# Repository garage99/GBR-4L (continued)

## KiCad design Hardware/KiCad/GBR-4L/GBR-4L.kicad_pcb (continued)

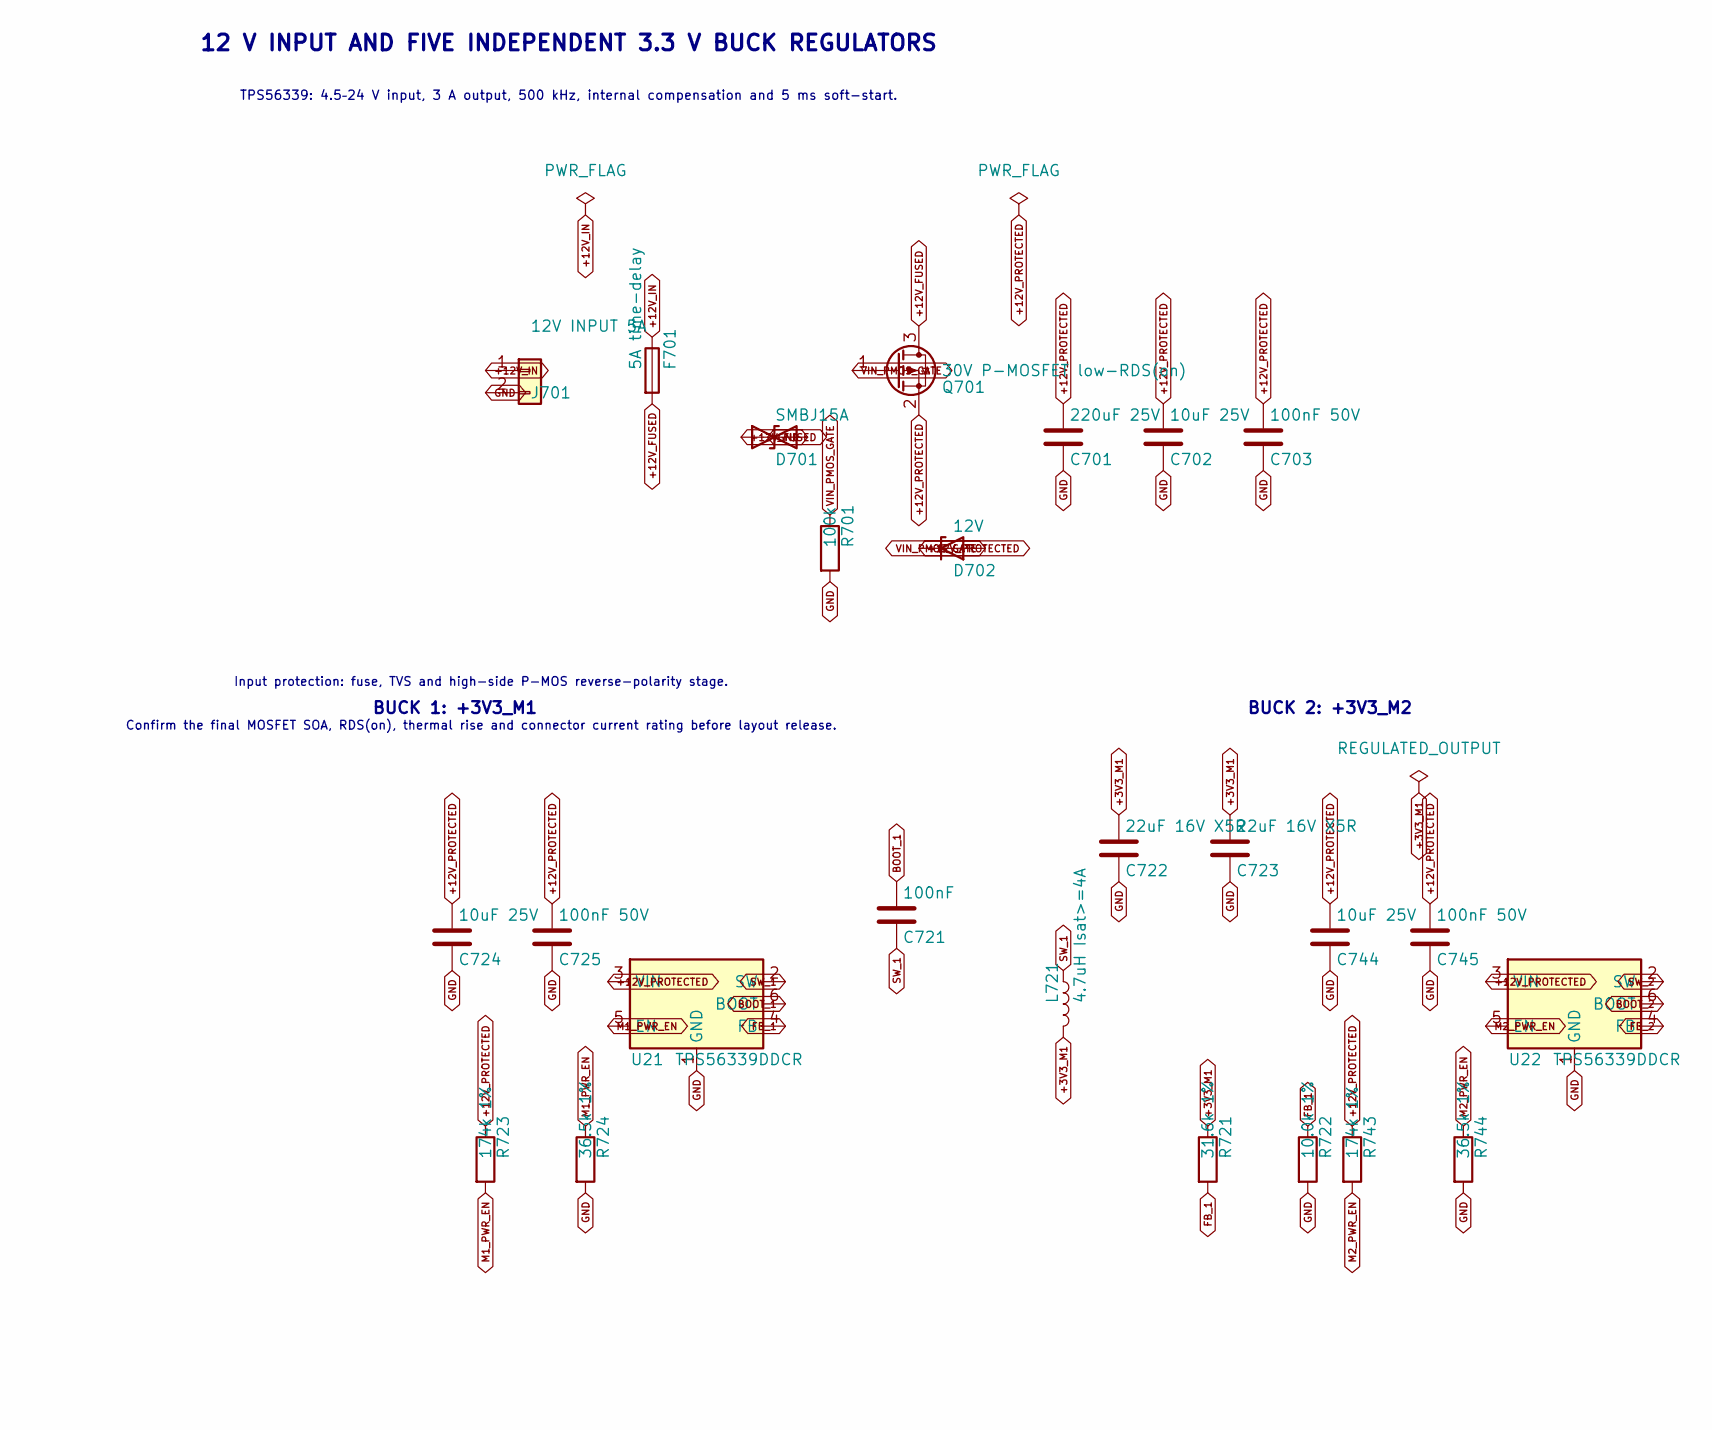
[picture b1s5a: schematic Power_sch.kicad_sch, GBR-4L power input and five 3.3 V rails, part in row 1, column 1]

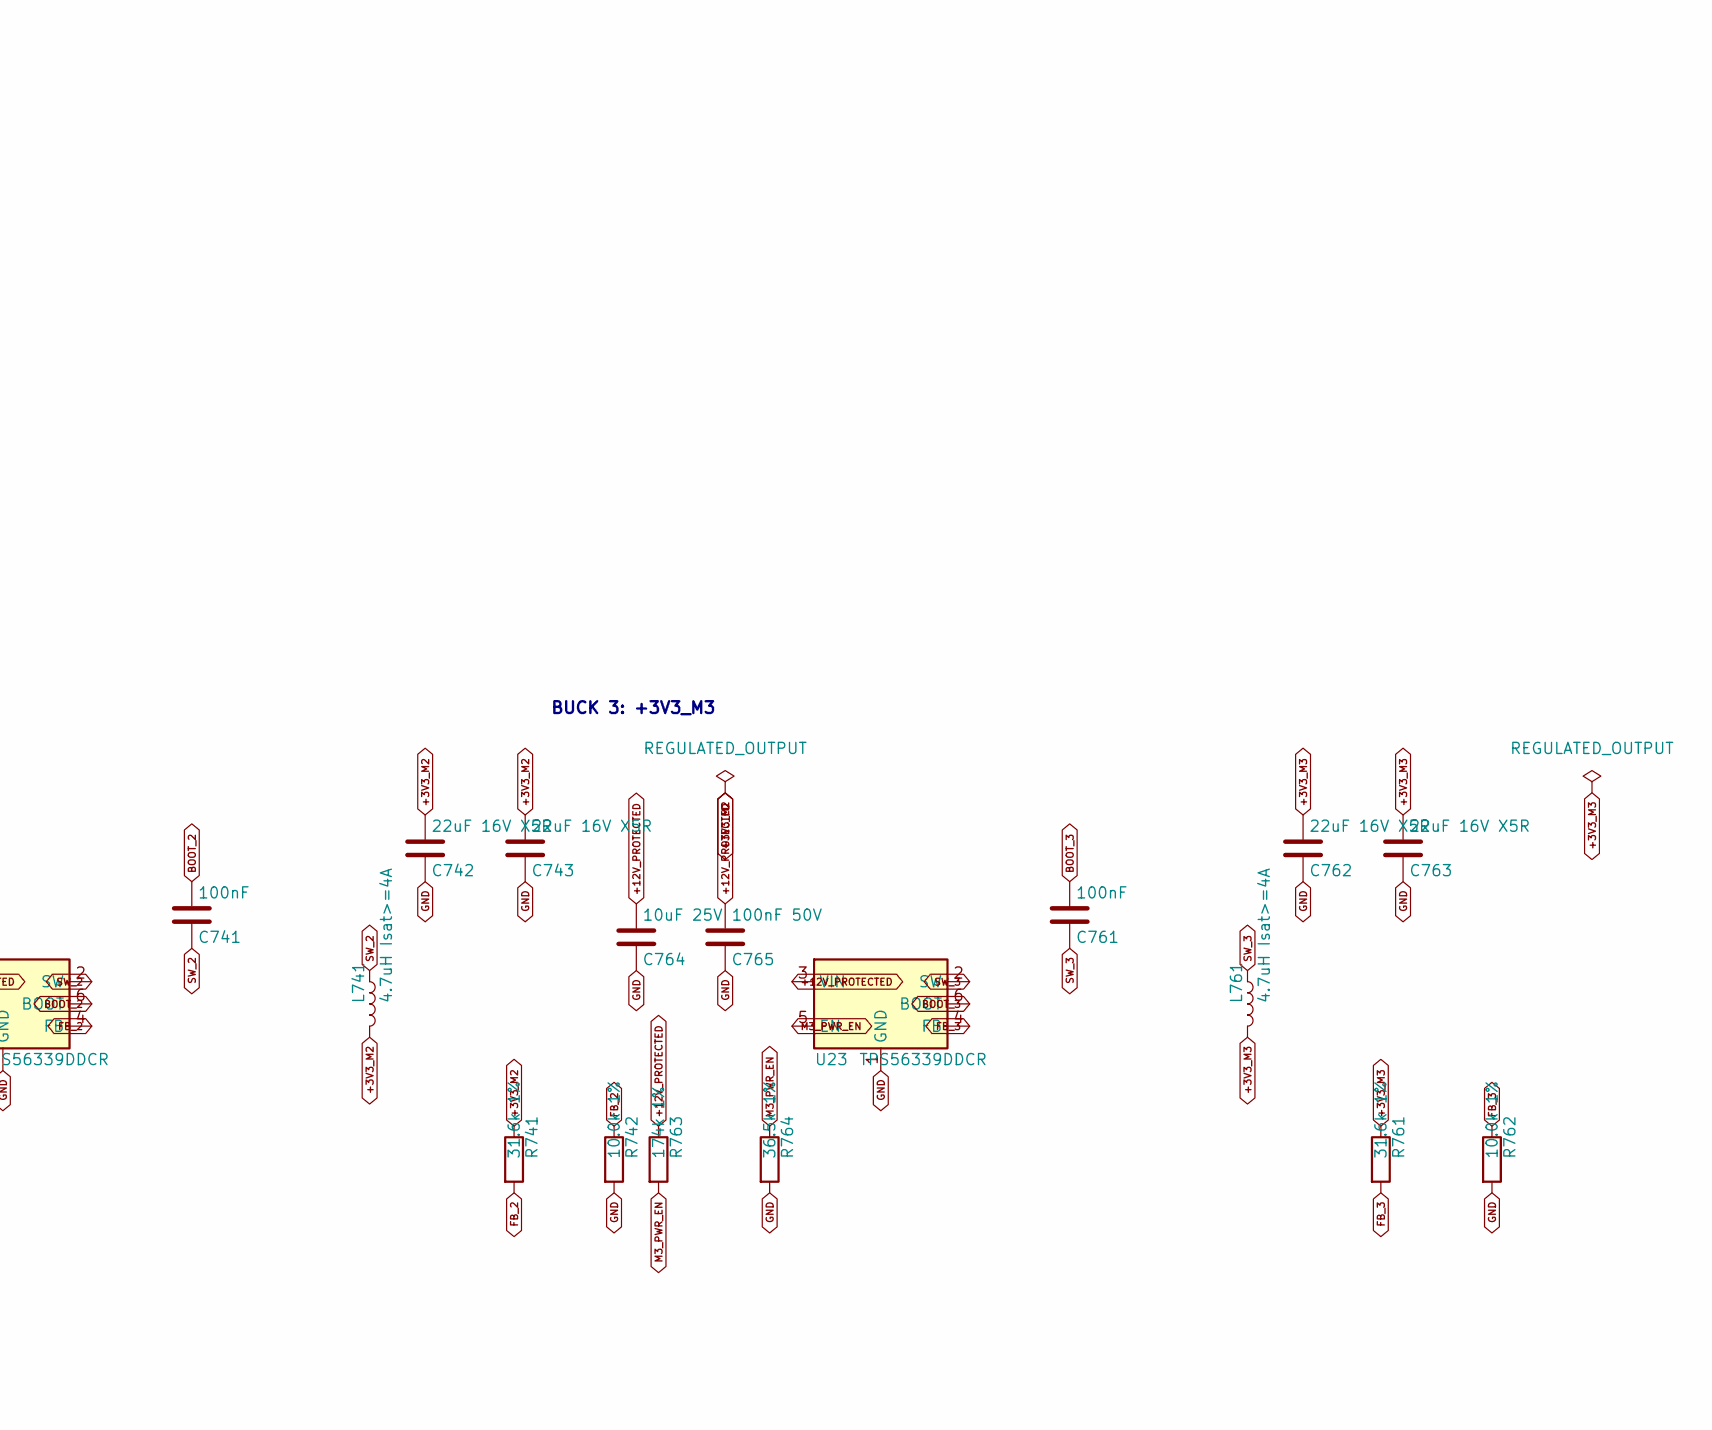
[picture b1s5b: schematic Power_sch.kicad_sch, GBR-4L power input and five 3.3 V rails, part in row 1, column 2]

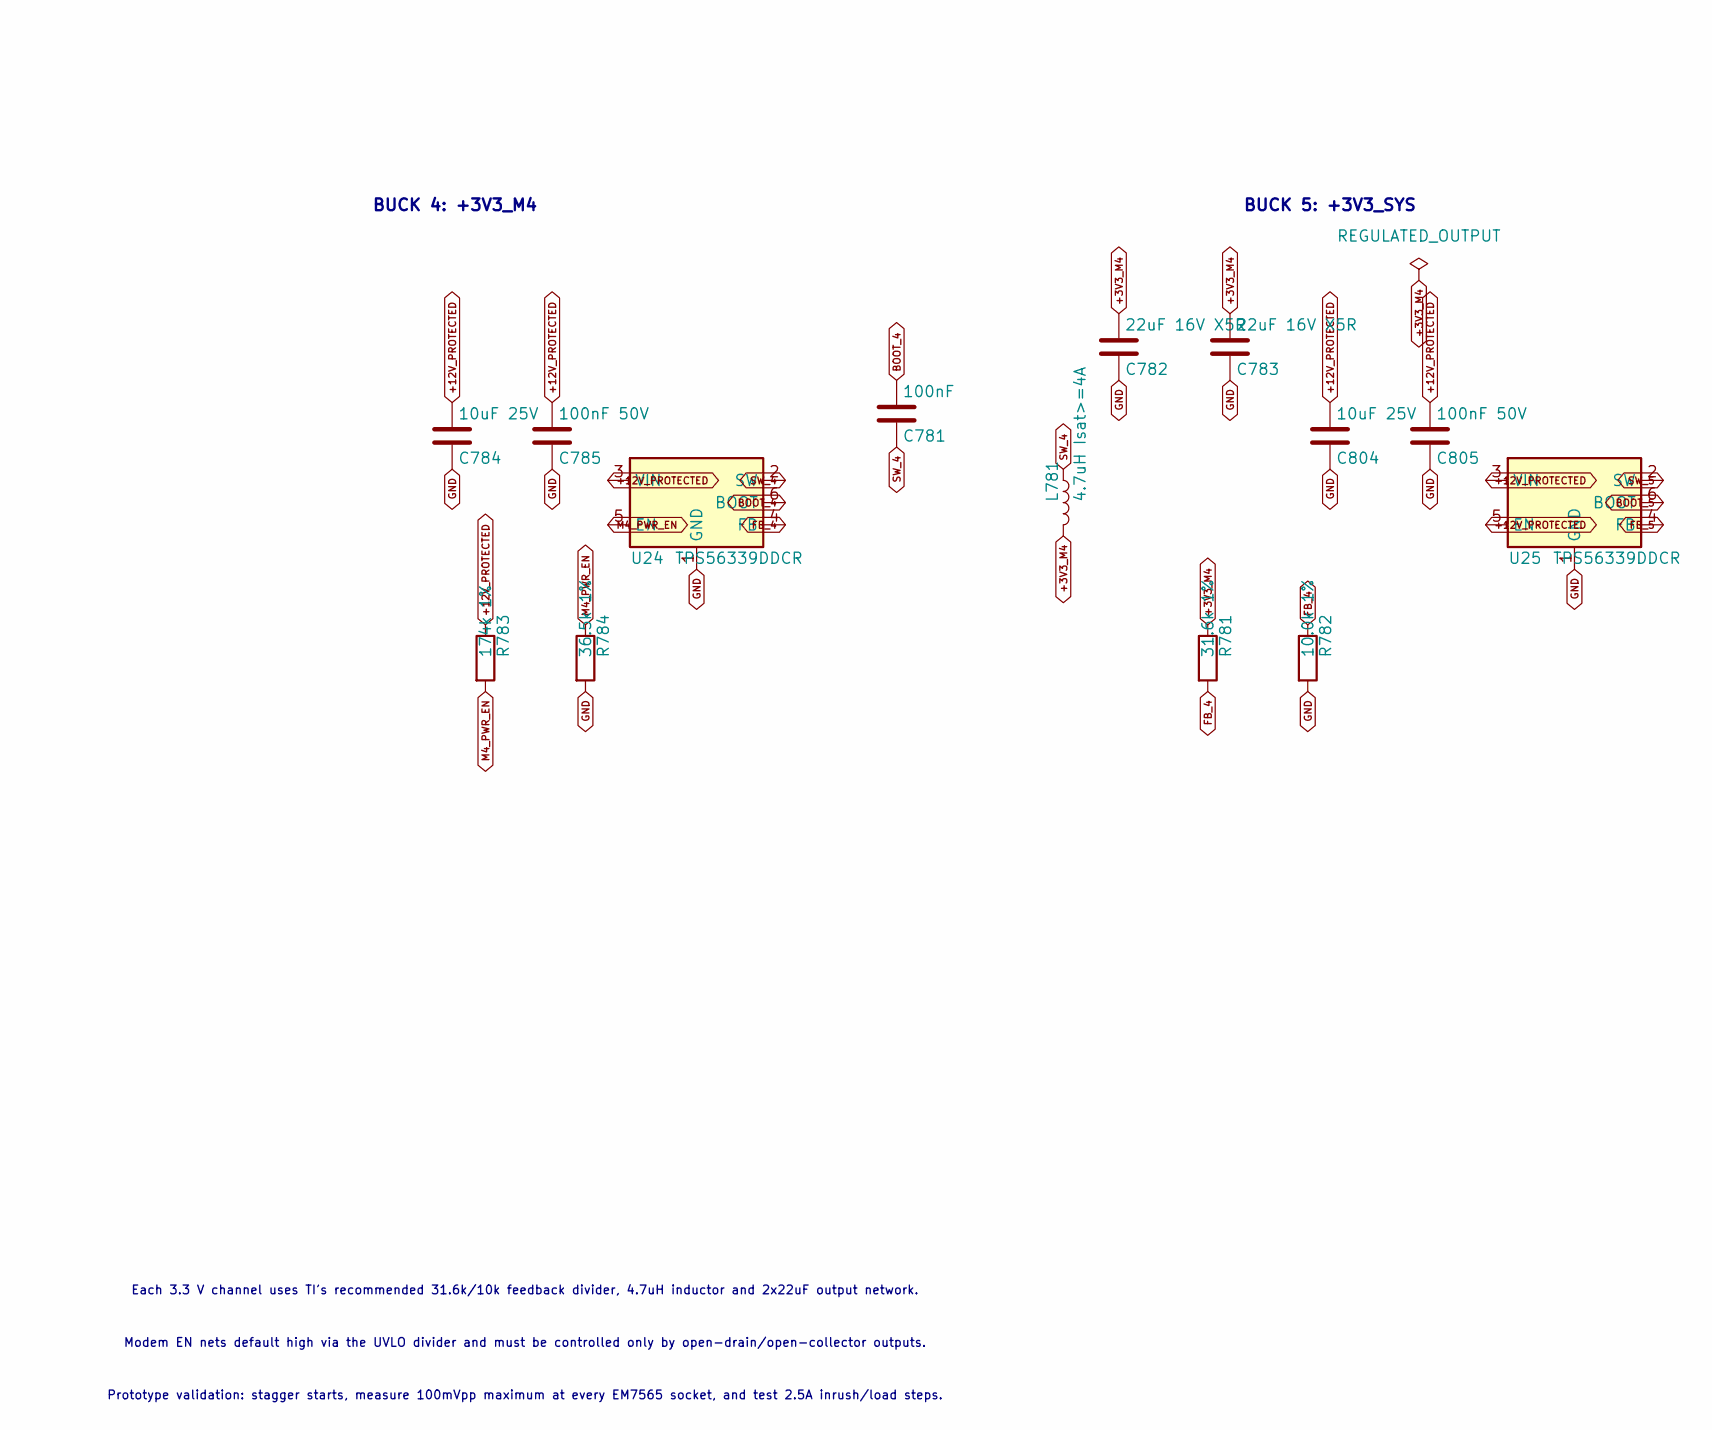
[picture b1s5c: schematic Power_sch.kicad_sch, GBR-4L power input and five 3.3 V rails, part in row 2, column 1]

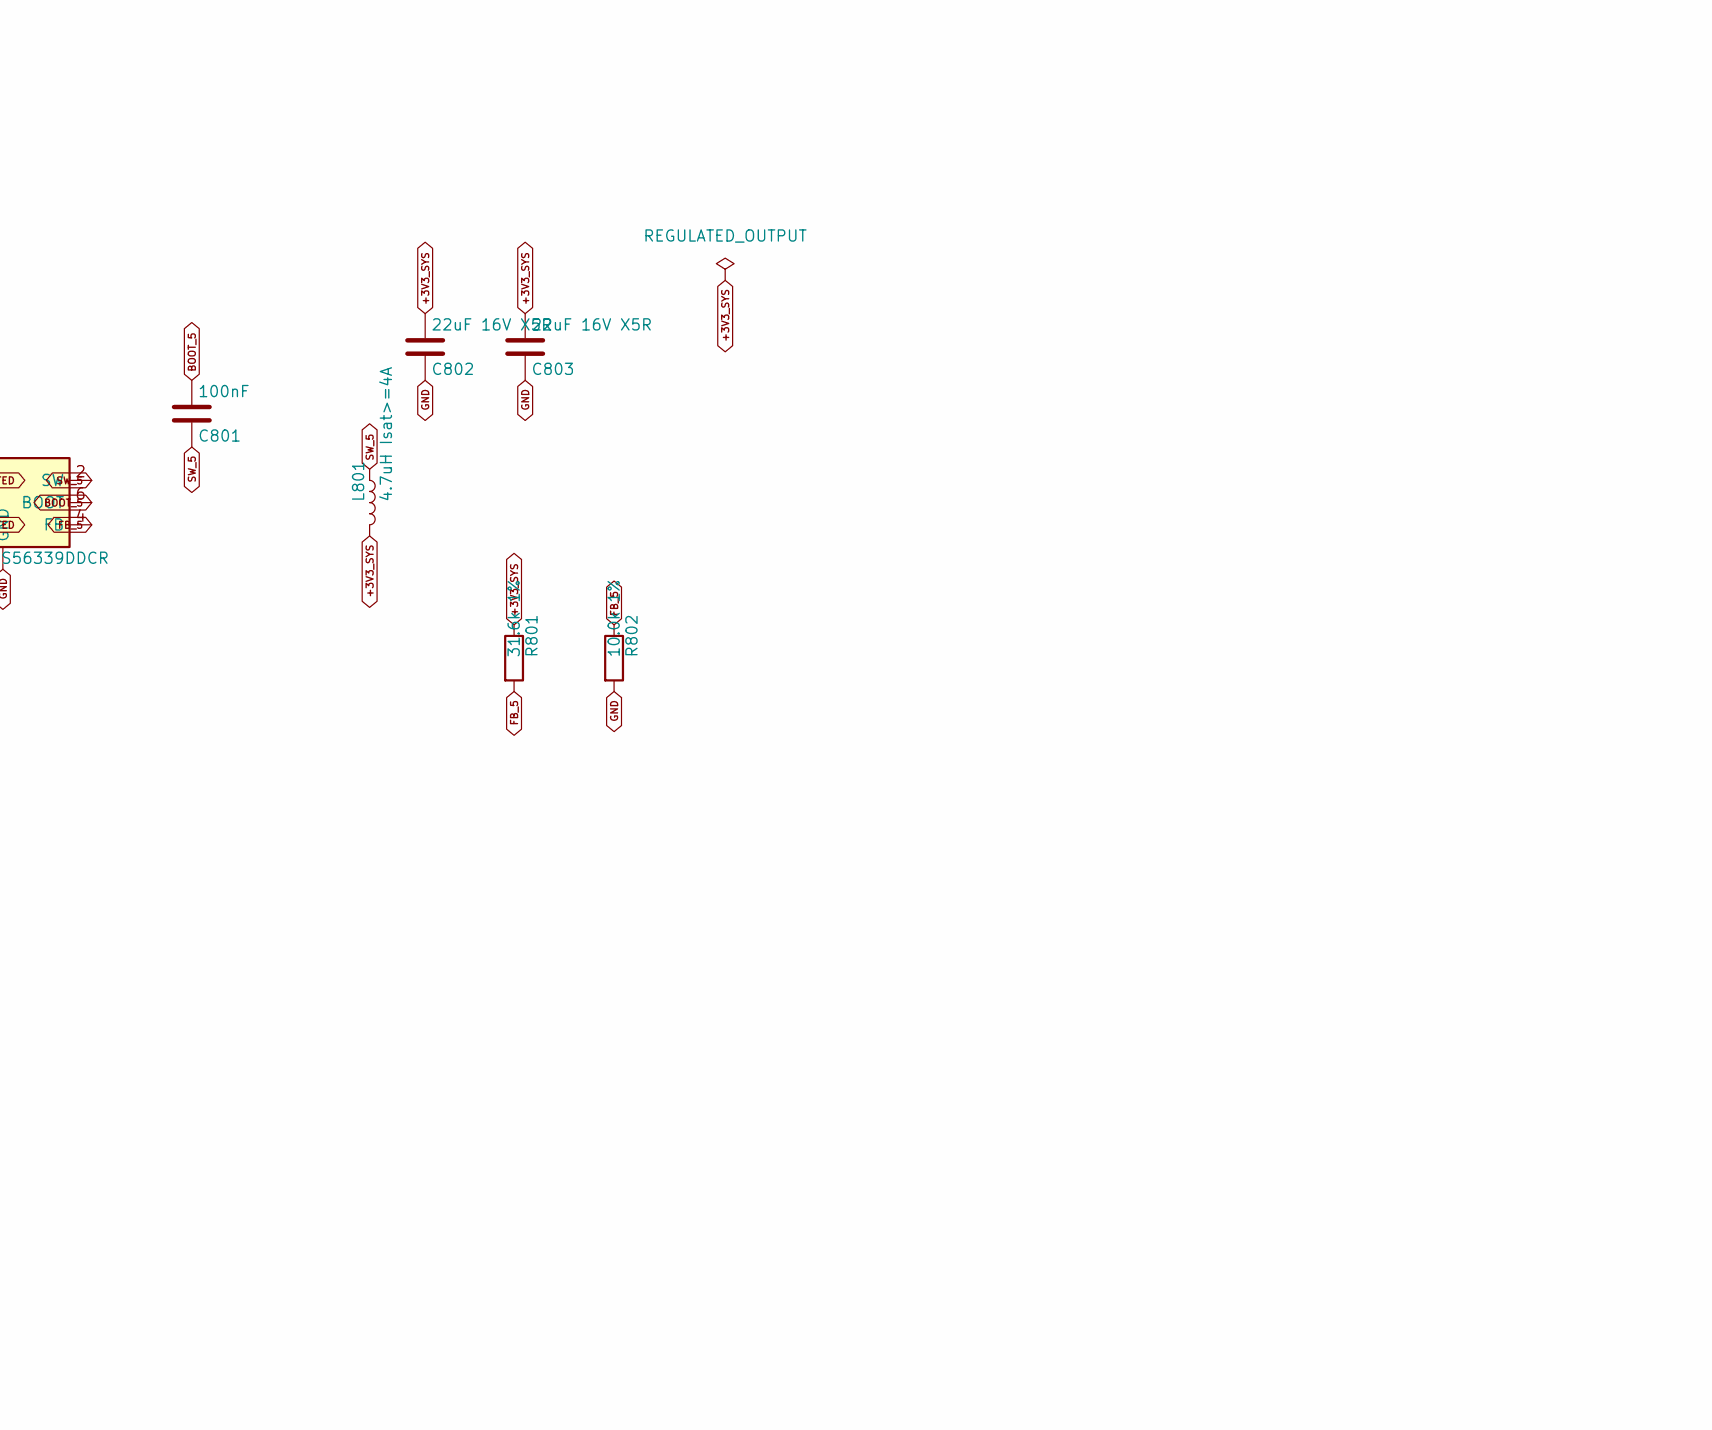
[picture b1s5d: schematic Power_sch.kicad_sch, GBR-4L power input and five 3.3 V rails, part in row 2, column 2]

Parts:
C701: 220uF 25V; C_Elec_10x10.2
C702: 10uF 25V; C_1210_3225Metric
C703, C725, C745, C765, C785, C805: 100nF 50V; C_0603_1608Metric
C721, C741, C761, C781, C801: 100nF; C_0603_1608Metric
C722, C723, C742, C743, C762, C763, C782, C783, C802, C803: 22uF 16V X5R; C_0805_2012Metric
C724, C744, C764, C784, C804: 10uF 25V; C_0805_2012Metric
D701: SMBJ15A; D_SMB
D702: 12V; D_SOD-123
F701: 5A time-delay; Fuseholder_Blade_ATO_Littelfuse_Pudenz_2_Pin
J701: 12V INPUT 5A; TerminalBlock_Phoenix_MKDS-1,5-2_1x02_P5.00mm_Horizontal
L721, L741, L761, L781, L801: 4.7uH Isat>=4A; L_7.3x7.3_H3.5
Q701: 30V P-MOSFET low-RDS(on); TO-252-2
R701: 100k; R_0603_1608Metric
R721, R741, R761, R781, R801: 31.6k 1%; R_0603_1608Metric
R722, R742, R762, R782, R802: 10.0k 1%; R_0603_1608Metric
R723, R743, R763, R783: 174k 1%; R_0603_1608Metric
R724, R744, R764, R784: 36.5k 1%; R_0603_1608Metric
U21, U22, U23, U24, U25: TPS56339DDCR; SOT-23-6

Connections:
+3V3_M1: C722.1, C723.1, L721.2, R721.1; also elsewhere on the board
+3V3_M2: C742.1, C743.1, L741.2, R741.1; also elsewhere on the board
+3V3_M3: C762.1, C763.1, L761.2, R761.1; also elsewhere on the board
+3V3_M4: C782.1, C783.1, L781.2, R781.1; also elsewhere on the board
+3V3_SYS: C802.1, C803.1, L801.2, R801.1; also elsewhere on the board
+12V_FUSED: D701.1 (A1), F701.2, Q701.3 (D)
+12V_IN: F701.1, J701.1
+12V_PROTECTED: C701.1, C702.1, C703.1, C724.1, C725.1, C744.1, C745.1, C764.1, C765.1, C784.1, C785.1, C804.1, C805.1, D702.1 (K), Q701.2 (S), R723.1, R743.1, R763.1, R783.1, U21.3 (VIN), U22.3 (VIN), U23.3 (VIN), U24.3 (VIN), U25.3 (VIN), U25.5 (EN)
BOOT_1: C721.1, U21.6 (BOOT)
BOOT_2: C741.1, U22.6 (BOOT)
BOOT_3: C761.1, U23.6 (BOOT)
BOOT_4: C781.1, U24.6 (BOOT)
BOOT_5: C801.1, U25.6 (BOOT)
FB_1: R721.2, R722.1, U21.4 (FB)
FB_2: R741.2, R742.1, U22.4 (FB)
FB_3: R761.2, R762.1, U23.4 (FB)
FB_4: R781.2, R782.1, U24.4 (FB)
FB_5: R801.2, R802.1, U25.4 (FB)
GND: C701.2, C702.2, C703.2, C722.2, C723.2, C724.2, C725.2, C742.2, C743.2, C744.2, C745.2, C762.2, C763.2, C764.2, C765.2, C782.2, C783.2, C784.2, C785.2, C802.2, C803.2, C804.2, C805.2, D701.2 (A2), J701.2, R701.2, R722.2, R724.2, R742.2, R744.2, R762.2, R764.2, R782.2, R784.2, R802.2, U21.1 (GND), U22.1 (GND), U23.1 (GND), U24.1 (GND), U25.1 (GND); also elsewhere on the board
M1_PWR_EN: R723.2, R724.1, U21.5 (EN); also elsewhere on the board
M2_PWR_EN: R743.2, R744.1, U22.5 (EN); also elsewhere on the board
M3_PWR_EN: R763.2, R764.1, U23.5 (EN); also elsewhere on the board
M4_PWR_EN: R783.2, R784.1, U24.5 (EN); also elsewhere on the board
SW_1: C721.2, L721.1, U21.2 (SW)
SW_2: C741.2, L741.1, U22.2 (SW)
SW_3: C761.2, L761.1, U23.2 (SW)
SW_4: C781.2, L781.1, U24.2 (SW)
SW_5: C801.2, L801.1, U25.2 (SW)
VIN_PMOS_GATE: D702.2 (A), Q701.1 (G), R701.1

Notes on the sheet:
Input protection: fuse, TVS and high-side P-MOS reverse-polarity stage.
Prototype validation: stagger starts, measure 100mVpp maximum at every EM7565 socket, and test 2.5A inrush/load steps.
BUCK 1: +3V3_M1
BUCK 4: +3V3_M4
Modem EN nets default high via the UVLO divider and must be controlled only by open-drain/open-collector outputs.
12 V INPUT AND FIVE INDEPENDENT 3.3 V BUCK REGULATORS
TPS56339: 4.5–24 V input, 3 A output, 500 kHz, internal compensation and 5 ms soft-start.
BUCK 5: +3V3_SYS
BUCK 3: +3V3_M3
Confirm the final MOSFET SOA, RDS(on), thermal rise and connector current rating before layout release.
BUCK 2: +3V3_M2
Each 3.3 V channel uses TI's recommended 31.6k/10k feedback divider, 4.7uH inductor and 2x22uF output network.

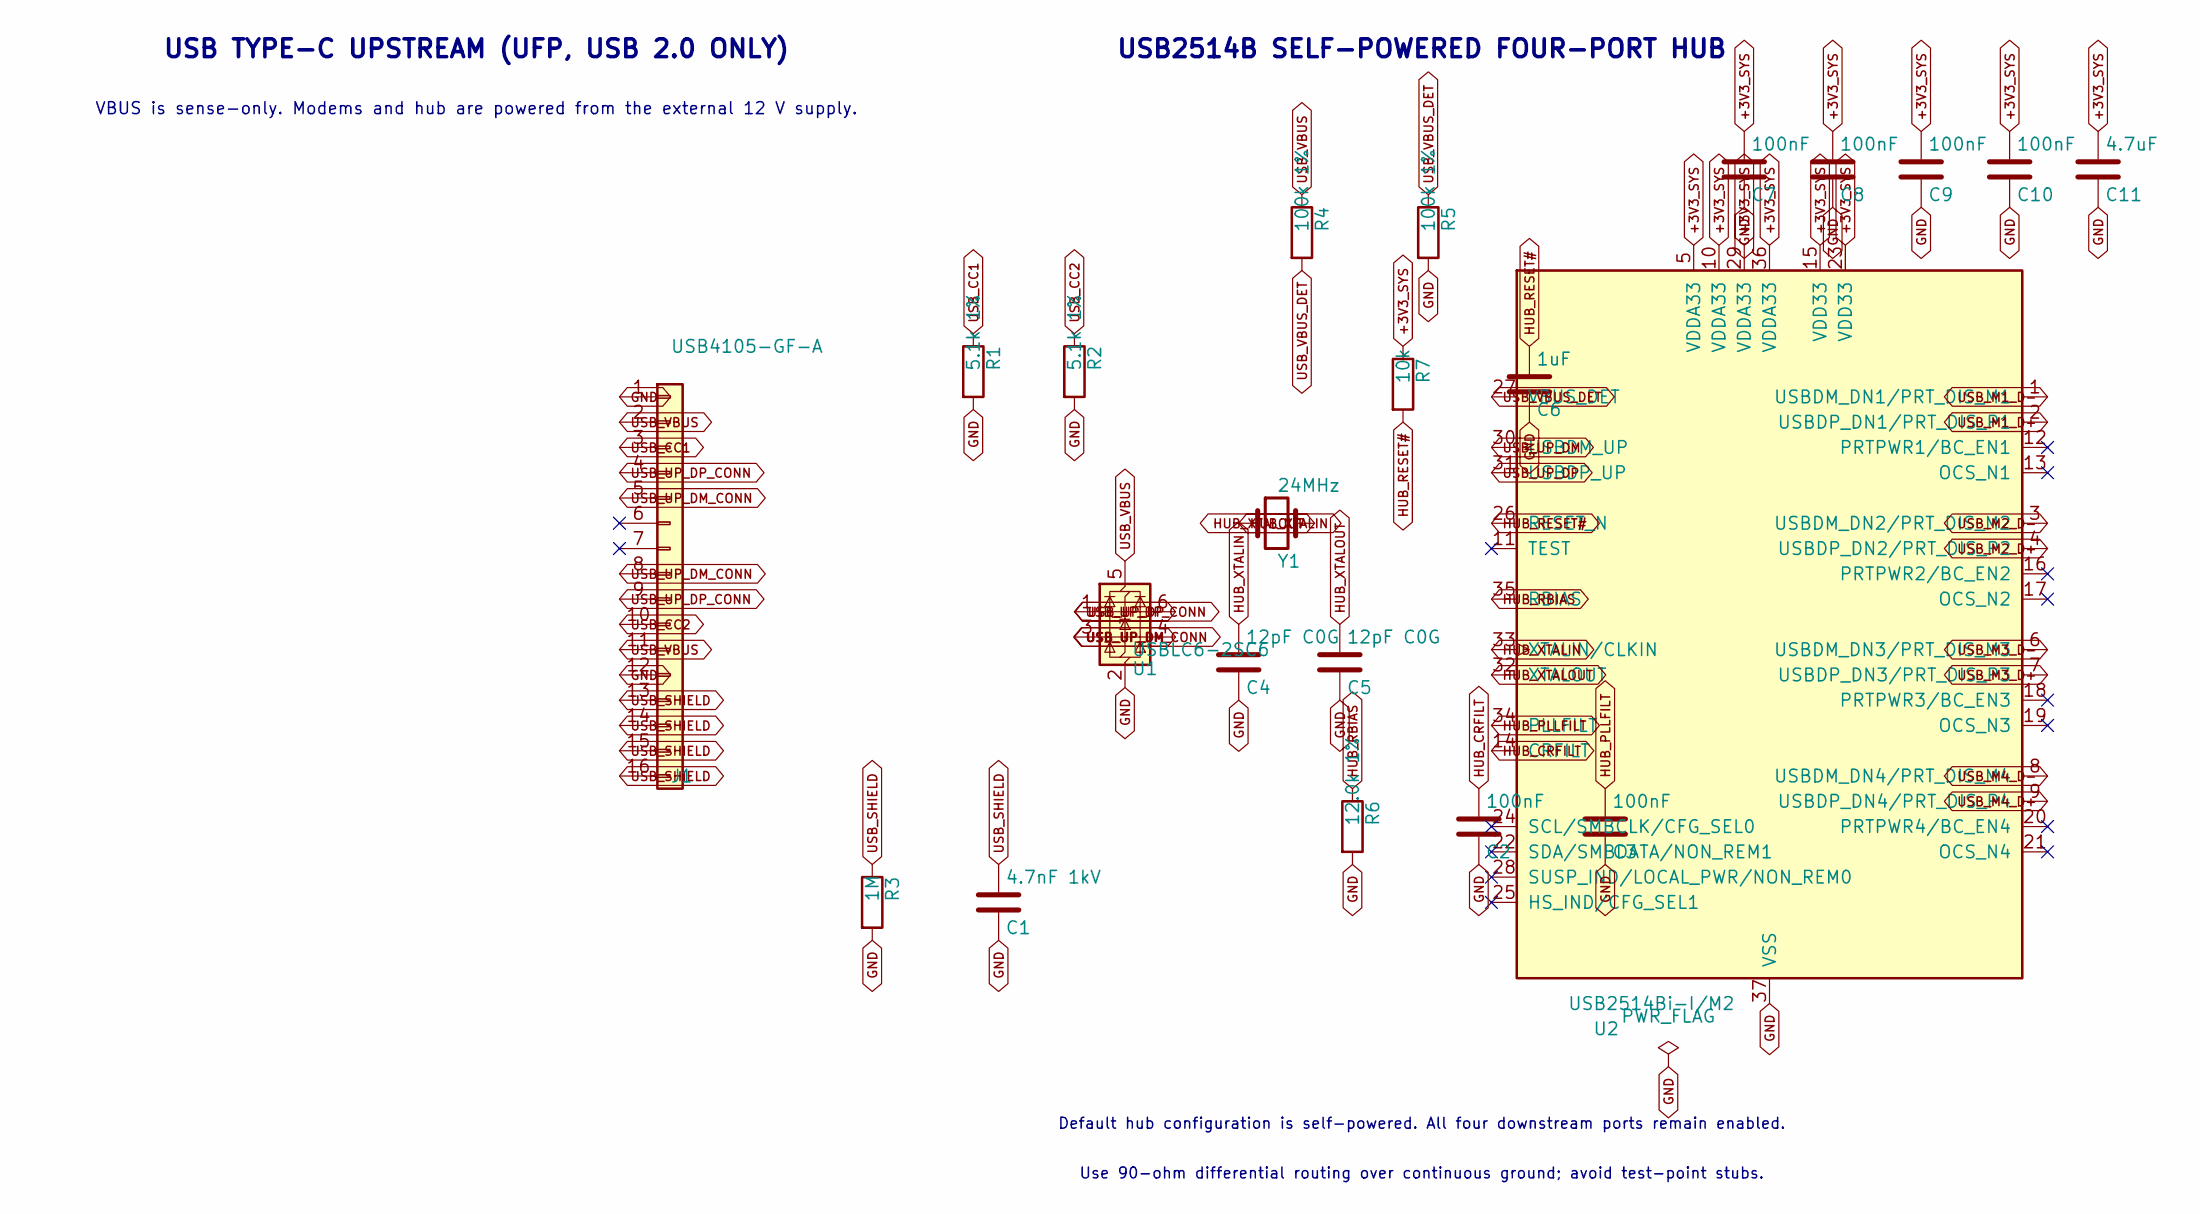
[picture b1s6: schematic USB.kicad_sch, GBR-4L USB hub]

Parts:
C1: 4.7nF 1kV; C_1206_3216Metric
C2, C3, C7, C8, C9, C10: 100nF; C_0603_1608Metric
C4, C5: 12pF C0G; C_0603_1608Metric
C6: 1uF; C_0603_1608Metric
C11: 4.7uF; C_0805_2012Metric
J1: USB4105-GF-A; GCT_USB4105-16P_MergedTails
R1, R2: 5.1k 1%; R_0603_1608Metric
R3: 1M; R_0603_1608Metric
R4, R5: 100k 1%; R_0603_1608Metric
R6: 12.0k 1%; R_0603_1608Metric
R7: 10k; R_0603_1608Metric
U1: USBLC6-2SC6; SOT-23-6
U2: USB2514Bi-I/M2; QFN-36-1EP_6x6mm_P0.5mm_EP4.1x4.1mm
Y1: 24MHz; Crystal_SMD_3225-4Pin_3.2x2.5mm

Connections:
+3V3_SYS: C7.1, C8.1, C9.1, C10.1, C11.1, R7.1, U2.5 (VDDA33), U2.10 (VDDA33), U2.15 (VDD33), U2.23 (VDD33), U2.29 (VDDA33), U2.36 (VDDA33); also elsewhere on the board
GND: C1.2, C2.2, C3.2, C4.2, C5.2, C6.2, C7.2, C8.2, C9.2, C10.2, C11.2, J1.1, J1.12, R1.2, R2.2, R3.2, R5.2, R6.2, U1.2 (GND), U2.37 (VSS); also elsewhere on the board
HUB_CRFILT: C2.1, U2.14 (CRFILT)
HUB_PLLFILT: C3.1, U2.34 (PLLFILT)
HUB_RBIAS: R6.1, U2.35 (RBIAS)
HUB_RESET#: C6.1, R7.2, U2.26 (RESET_N)
HUB_XTALIN: C4.1, U2.33 (XTALIN/CLKIN), Y1.1
HUB_XTALOUT: C5.1, U2.32 (XTALOUT), Y1.2
USB_CC1: J1.3, R1.1
USB_CC2: J1.10, R2.1
USB_M1_D+: U2.2 (USBDP_DN1/PRT_DIS_P1); also elsewhere on the board
USB_M1_D-: U2.1 (USBDM_DN1/PRT_DIS_M1); also elsewhere on the board
USB_M2_D+: U2.4 (USBDP_DN2/PRT_DIS_P2); also elsewhere on the board
USB_M2_D-: U2.3 (USBDM_DN2/PRT_DIS_M2); also elsewhere on the board
USB_M3_D+: U2.7 (USBDP_DN3/PRT_DIS_P3); also elsewhere on the board
USB_M3_D-: U2.6 (USBDM_DN3/PRT_DIS_M3); also elsewhere on the board
USB_M4_D+: U2.9 (USBDP_DN4/PRT_DIS_P4); also elsewhere on the board
USB_M4_D-: U2.8 (USBDM_DN4/PRT_DIS_M4); also elsewhere on the board
USB_SHIELD: C1.1, J1.13, J1.14, J1.15, J1.16, R3.1
USB_UP_DM: U1.4 (I/O2), U2.30 (USBDM_UP)
USB_UP_DM_CONN: J1.5, J1.8, U1.3 (I/O2)
USB_UP_DP: U1.6 (I/O1), U2.31 (USBDP_UP)
USB_UP_DP_CONN: J1.4, J1.9, U1.1 (I/O1)
USB_VBUS: J1.2, J1.11, R4.1, U1.5 (VBUS)
USB_VBUS_DET: R4.2, R5.1, U2.27 (VBUS_DET)

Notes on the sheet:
USB TYPE-C UPSTREAM (UFP, USB 2.0 ONLY)
USB2514B SELF-POWERED FOUR-PORT HUB
VBUS is sense-only. Modems and hub are powered from the external 12 V supply.
Default hub configuration is self-powered. All four downstream ports remain enabled.
Use 90-ohm differential routing over continuous ground; avoid test-point stubs.

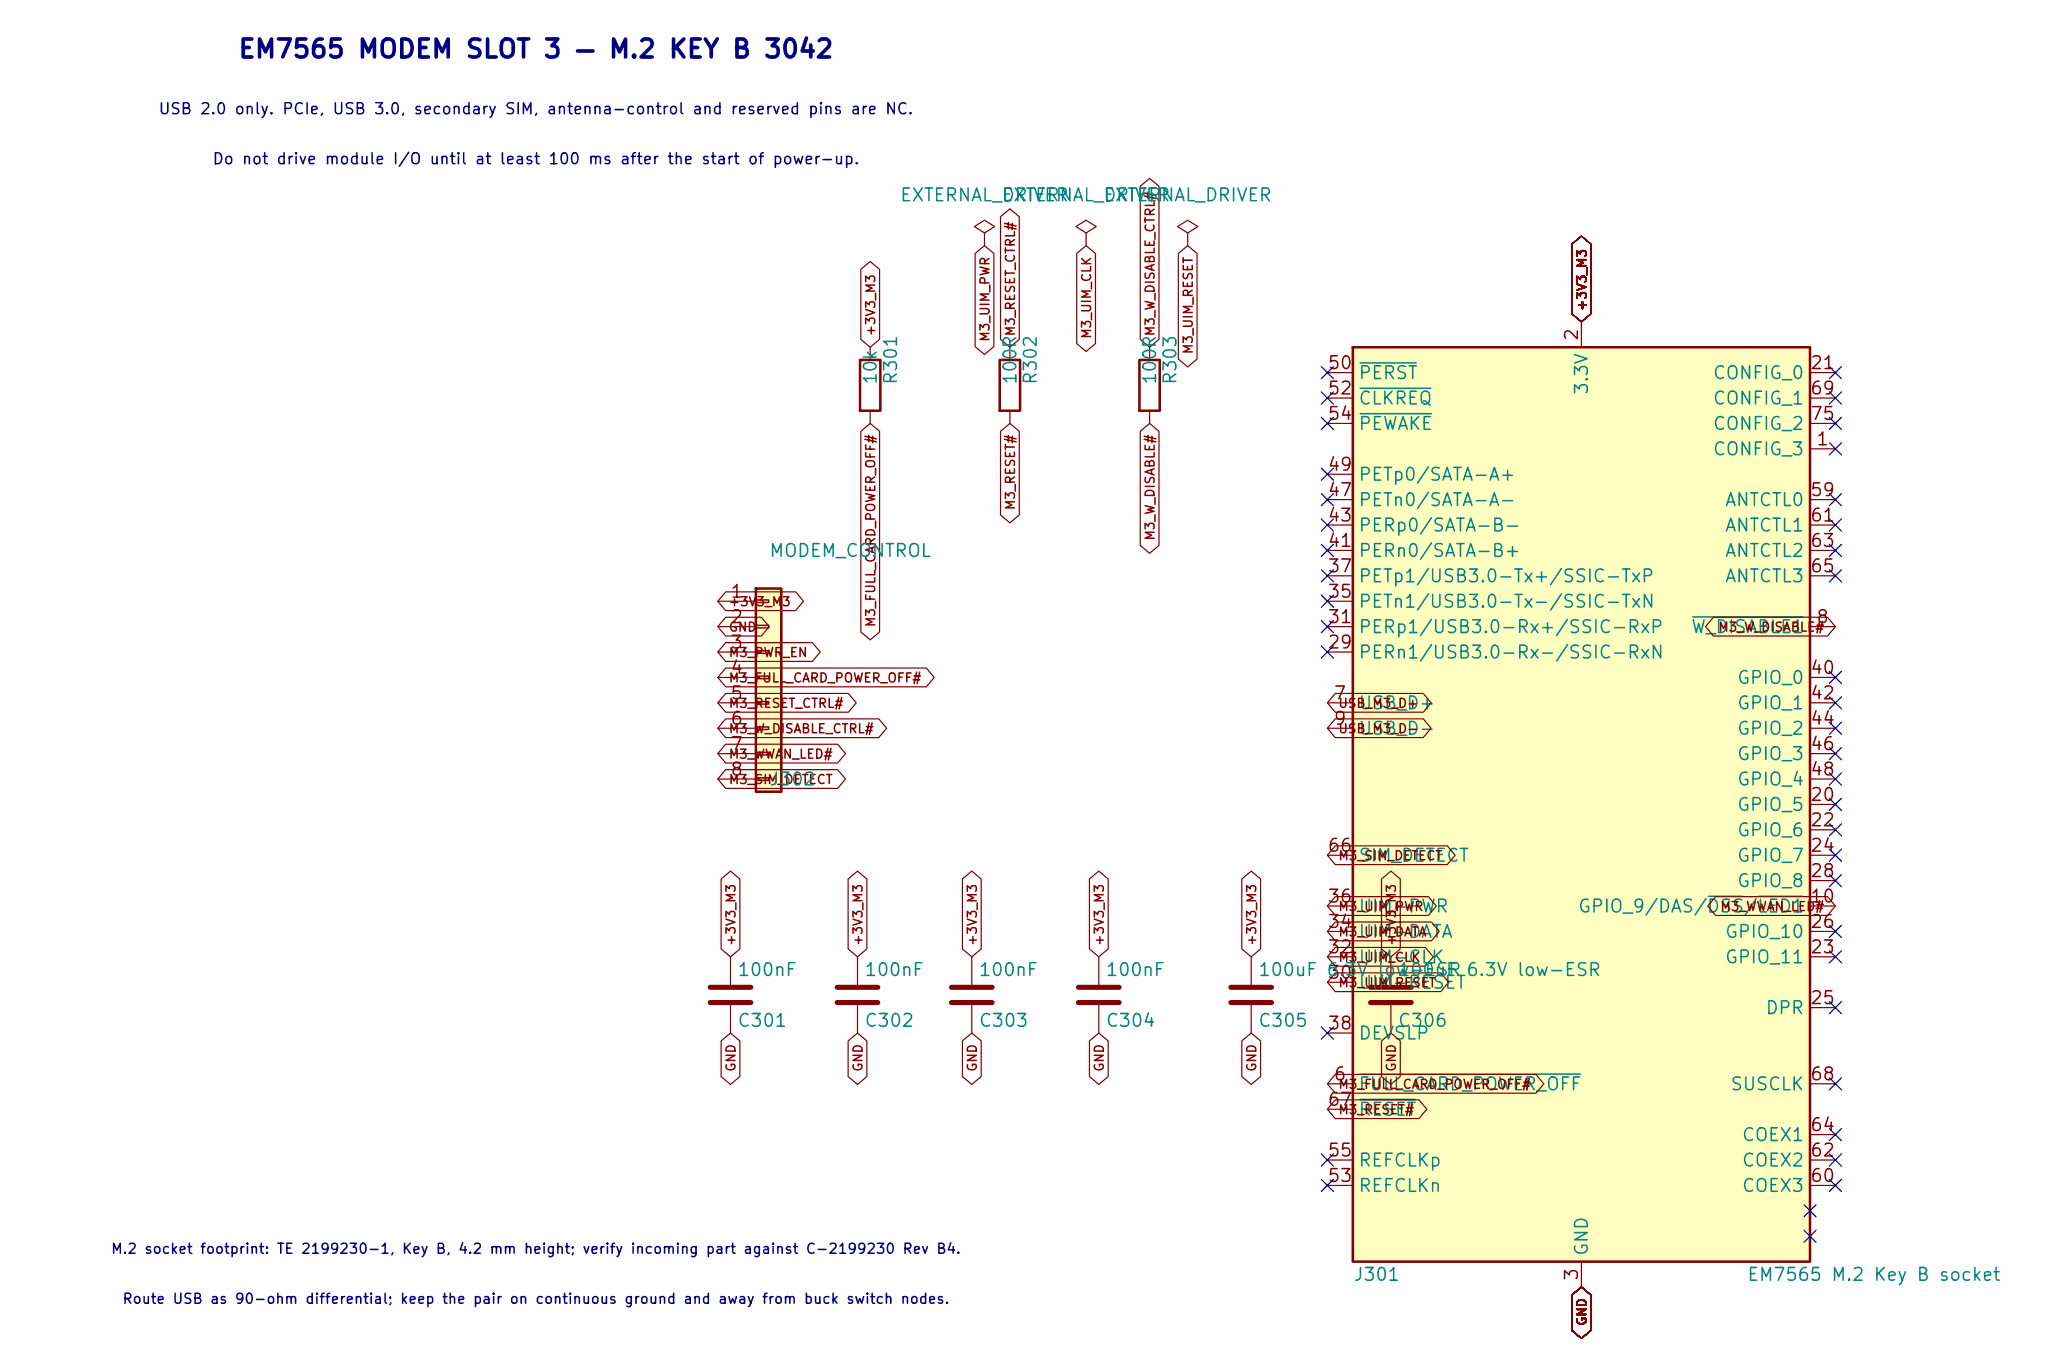
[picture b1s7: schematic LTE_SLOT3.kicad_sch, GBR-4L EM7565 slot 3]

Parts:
C301, C302, C303, C304: 100nF; C_0603_1608Metric
C305, C306: 100uF 6.3V low-ESR; C_1210_3225Metric
J301: EM7565 M.2 Key B socket; TE_2199230-1_M2_Key-B
J302: MODEM_CONTROL; PinHeader_1x08_P2.54mm_Vertical
R301: 10k; R_0603_1608Metric
R302, R303: 100R; R_0603_1608Metric

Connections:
+3V3_M3: C301.1, C302.1, C303.1, C304.1, C305.1, C306.1, J301.2 (3.3V), J301.4 (3.3V), J301.70 (3.3V), J301.72 (3.3V), J301.74 (3.3V), J302.1, R301.1; also elsewhere on the board
GND: C301.2, C302.2, C303.2, C304.2, C305.2, C306.2, J301.3 (GND), J301.5 (GND), J301.11 (GND), J301.27 (GND), J301.33 (GND), J301.39 (GND), J301.45 (GND), J301.51 (GND), J301.57 (GND), J301.71 (GND), J301.73 (GND), J302.2; also elsewhere on the board
M3_FULL_CARD_POWER_OFF#: J301.6 (~FULL_CARD_POWER_OFF), J302.4, R301.2
M3_PWR_EN: J302.3; also elsewhere on the board
M3_RESET#: J301.67 (~RESET), R302.2
M3_RESET_CTRL#: J302.5, R302.1; also elsewhere on the board
M3_SIM_DETECT: J301.66 (SIM_DETECT), J302.8; also elsewhere on the board
M3_UIM_CLK: J301.32 (UIM-CLK); also elsewhere on the board
M3_UIM_DATA: J301.34 (UIM-DATA); also elsewhere on the board
M3_UIM_PWR: J301.36 (UIM-PWR); also elsewhere on the board
M3_UIM_RESET: J301.30 (UIM-RESET); also elsewhere on the board
M3_WWAN_LED#: J301.10 (GPIO_9/DAS/~DSS/~LED1), J302.7; also elsewhere on the board
M3_W_DISABLE#: J301.8 (~W_DISABLE1), R303.2
M3_W_DISABLE_CTRL#: J302.6, R303.1; also elsewhere on the board
USB_M3_D+: J301.7 (USB_D+); also elsewhere on the board
USB_M3_D-: J301.9 (USB_D-); also elsewhere on the board

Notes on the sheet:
M.2 socket footprint: TE 2199230-1, Key B, 4.2 mm height; verify incoming part against C-2199230 Rev B4.
Do not drive module I/O until at least 100 ms after the start of power-up.
EM7565 MODEM SLOT 3 — M.2 KEY B 3042
Route USB as 90-ohm differential; keep the pair on continuous ground and away from buck switch nodes.
USB 2.0 only. PCIe, USB 3.0, secondary SIM, antenna-control and reserved pins are NC.
